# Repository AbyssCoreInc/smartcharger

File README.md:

# smartcharger
Arduino Battery Charger

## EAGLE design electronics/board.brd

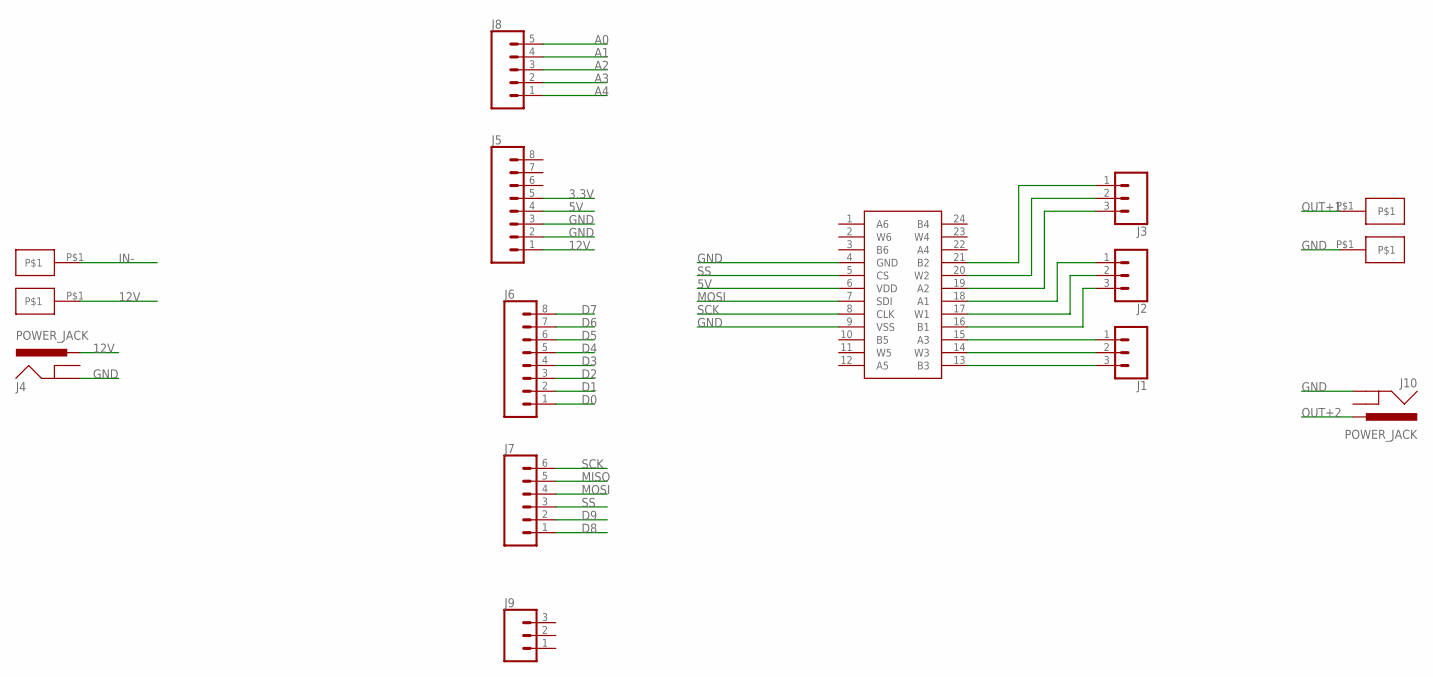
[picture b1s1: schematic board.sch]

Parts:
J1, J2, J3, J9: CONN_03; 1X03
J4, J10: POWER_JACK; POWER_JACK_PTH
J5, J6: CONN_08"; 1X08
J7: CONN_06SILK_FEMALE_PTH; 1X06
J8: CONN_05; 1X05
U$1: AD5206; TSSOP24
U$2, U$3, U$4, U$5: M012MM-HOLE; M01-2MM

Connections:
3.3V: J5.5
5V: J5.4, U$1.6 (VDD)
12V: J4.PWR, J5.1, U$3.P$1
A0: J8.5
A1: J8.4
A2: J8.3
A3: J8.2
A4: J8.1
D0: J6.1
D1: J6.2
D2: J6.3
D3: J6.4
D4: J6.5
D5: J6.6
D6: J6.7
D7: J6.8
D8: J7.1
D9: J7.2
GND: J4.GND, J5.2, J5.3, J10.GND, U$1.4 (GND), U$1.9 (VSS), U$5.P$1
IN-: U$2.P$1
MISO: J7.5
MOSI: J7.4, U$1.7 (SDI)
unnamed: J1.3, U$1.13 (B3)
unnamed: J1.2, U$1.14 (W3)
unnamed: J1.1, U$1.15 (A3)
unnamed: J2.3, U$1.16 (B1)
unnamed: J2.2, U$1.17 (W1)
unnamed: J2.1, U$1.18 (A1)
unnamed: J3.3, U$1.19 (A2)
unnamed: J3.2, U$1.20 (W2)
unnamed: J3.1, U$1.21 (B2)
OUT+1: U$4.P$1
OUT+2: J10.PWR
SCK: J7.6, U$1.8 (CLK)
SS: J7.3, U$1.5 (CS)

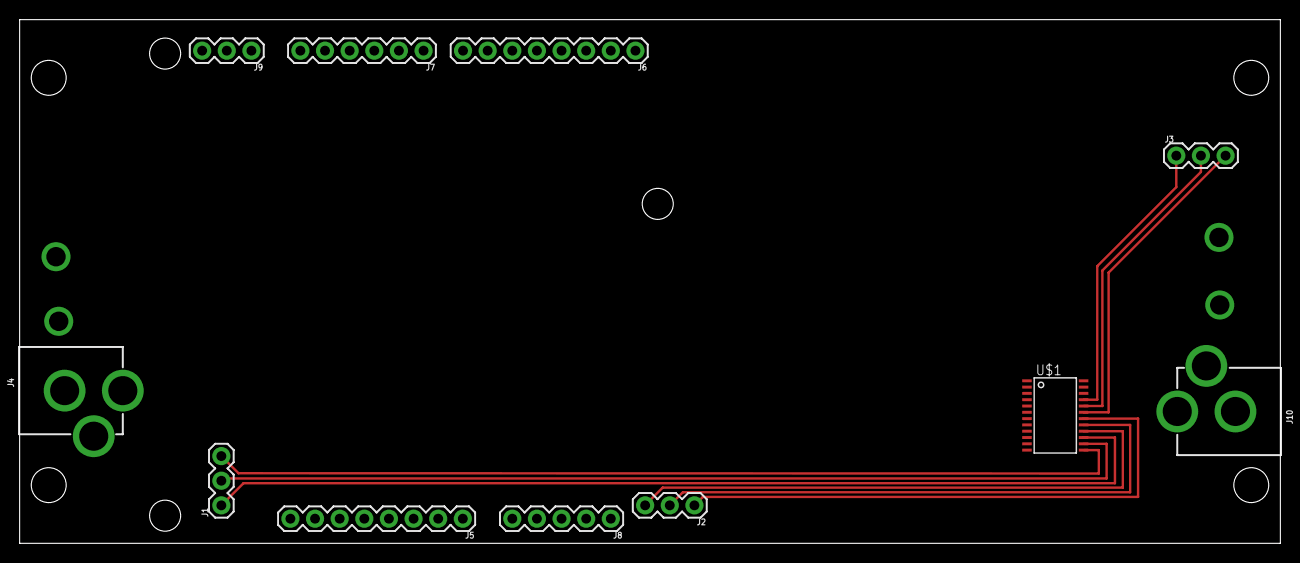
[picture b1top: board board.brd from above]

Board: 2 copper layers, 130.0 x 54.0 mm, 15 parts (0 on the bottom side), 15 nets.

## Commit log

2021-02-07 template board with arduino pinout
2021-02-11 small changes to initial board layout

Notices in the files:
parts and their libraries:
SparkFun-Connectors: Licensing: Creative Commons ShareAlike 4.0 International - https://creativecommons.org/licenses/by-sa/4.0
